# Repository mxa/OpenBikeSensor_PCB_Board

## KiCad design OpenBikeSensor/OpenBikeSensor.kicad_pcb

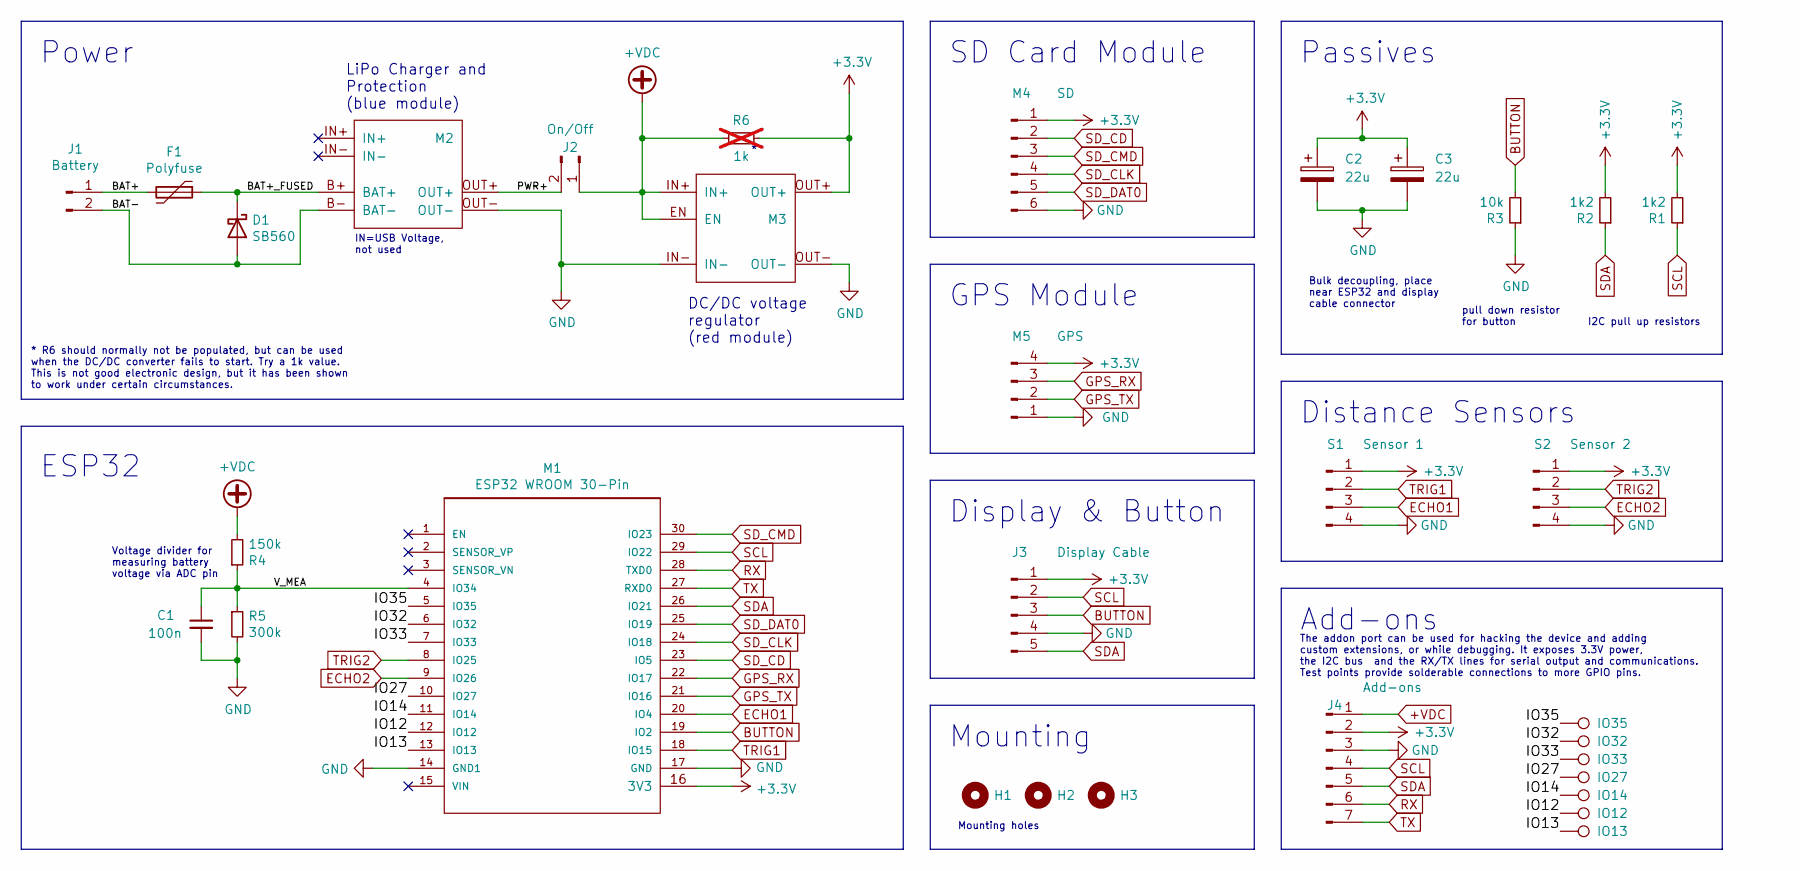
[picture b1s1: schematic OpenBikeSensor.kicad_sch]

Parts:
C1: 100n; C_Disc_D3.0mm_W1.6mm_P2.50mm
C2, C3: 22u; CP_Radial_D4.0mm_P1.50mm
D1: SB560; D_DO-201AD_P5.08mm_Vertical_KathodeUp
F1: Polyfuse; Fuse
H1, H2, H3: MountingHole; MountingHole_3.5mm
IO12: IO12; TestPoint_Pad_D1.0mm
IO13: IO13; TestPoint_Pad_D1.0mm
IO14: IO14; TestPoint_Pad_D1.0mm
IO27: IO27; TestPoint_Pad_D1.0mm
IO32: IO32; TestPoint_Pad_D1.0mm
IO33: IO33; TestPoint_Pad_D1.0mm
IO35: IO35; TestPoint_Pad_D1.0mm
J1: Battery; Connector_1x02
J2: On/Off; Connector_1x02_Switch
J3: Display Cable; Connector_1x05_Display
J4: Add-ons; Connector_1x07
M1: ESP32 WROOM 30-Pin; ESP32_WROOM_30_SMD
M2: LIPoChargerwithProtection; BATTERY-CHARGER-LI-PROT
M3: DCDC_fix; MT3608_SEPIC_DCDC_SMD
M4: SD; Connector_1x06
M5: GPS; Connector_1x04
R1, R2: 1k2; Resistor_Combined_THT3_SMD0805
R3: 10k; Resistor_Combined_THT3_SMD0805
R4: 150k; Resistor_Combined_THT3_SMD0805
R5: 300k; Resistor_Combined_THT3_SMD0805
R6: 1k; R_0603_1608Metric_Pad0.98x0.95mm_HandSolder; not fitted
S1: Sensor 1; Connector_1x04
S2: Sensor 2; Connector_1x04

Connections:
+3.3V: C2.1, C3.1, J3.1, J4.2, M1.16 (3V3), M3.OUT+, M4.1, M5.4, R1.2, R2.2, R6.2, S1.1, S2.1
+VDC: J2.1, J4.1, M3.EN, M3.IN+, R4.2, R6.1
/BAT+: F1.2, J1.1
/BAT+_FUSED: D1.1 (K), F1.1, M2.B+ (BAT+)
/BAT-: D1.2 (A), J1.2, M2.B- (BAT-)
/IO12: IO12.1, M1.12 (IO12)
/IO13: IO13.1, M1.13 (IO13)
/IO14: IO14.1, M1.11 (IO14)
/IO27: IO27.1, M1.10 (IO27)
/IO32: IO32.1, M1.6 (IO32)
/IO33: IO33.1, M1.7 (IO33)
/IO35: IO35.1, M1.5 (IO35)
/PWR+: J2.2, M2.OUT+
/V_MEA: C1.1, M1.4 (IO34), R4.1, R5.1
BUTTON: J3.3, M1.19 (IO2), R3.2
ECHO1: M1.20 (IO4), S1.3
ECHO2: M1.9 (IO26), S2.3
GND: C1.2, C2.2, C3.2, J3.4, J4.3, M1.14 (GND1), M1.17 (GND), M2.OUT-, M3.IN-, M3.OUT-, M4.6, M5.1, R3.1, R5.2, S1.4, S2.4
GPS_RX: M1.22 (IO17), M5.3
GPS_TX: M1.21 (IO16), M5.2
RX: J4.6, M1.28 (TXD0)
SCL: J3.2, J4.4, M1.29 (IO22), R1.1
SDA: J3.5, J4.5, M1.26 (IO21), R2.1
SD_CD: M1.23 (IO5), M4.2
SD_CLK: M1.24 (IO18), M4.4
SD_CMD: M1.30 (IO23), M4.3
SD_DAT0: M1.25 (IO19), M4.5
TRIG1: M1.18 (IO15), S1.2
TRIG2: M1.8 (IO25), S2.2
TX: J4.7, M1.27 (RXD0)

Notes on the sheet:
Mounting holes
Distance Sensors
Voltage divider for measuring battery voltage via ADC pin
Power
DC/DC voltage regulator (red module)
Display & Button
Bulk decoupling, place near ESP32 and display cable connector
Add-ons
GPS Module
pull down resistor for button
Passives
I2C pull up resistors
IN=USB Voltage, not used
Mounting
LiPo Charger and Protection (blue module)
SD Card Module
The addon port can be used for hacking the device and adding custom extensions, or while debugging. It exposes 3.3V power, the I2C bus and the RX/TX lines for serial output and communications. Test points provide solderable connections to more GPIO pins.
ESP32
* R6 should normally not be populated, but can be used when the DC/DC converter fails to start. Try a 1k value. This is not good electronic design, but it has been shown to work under certain circumstances.

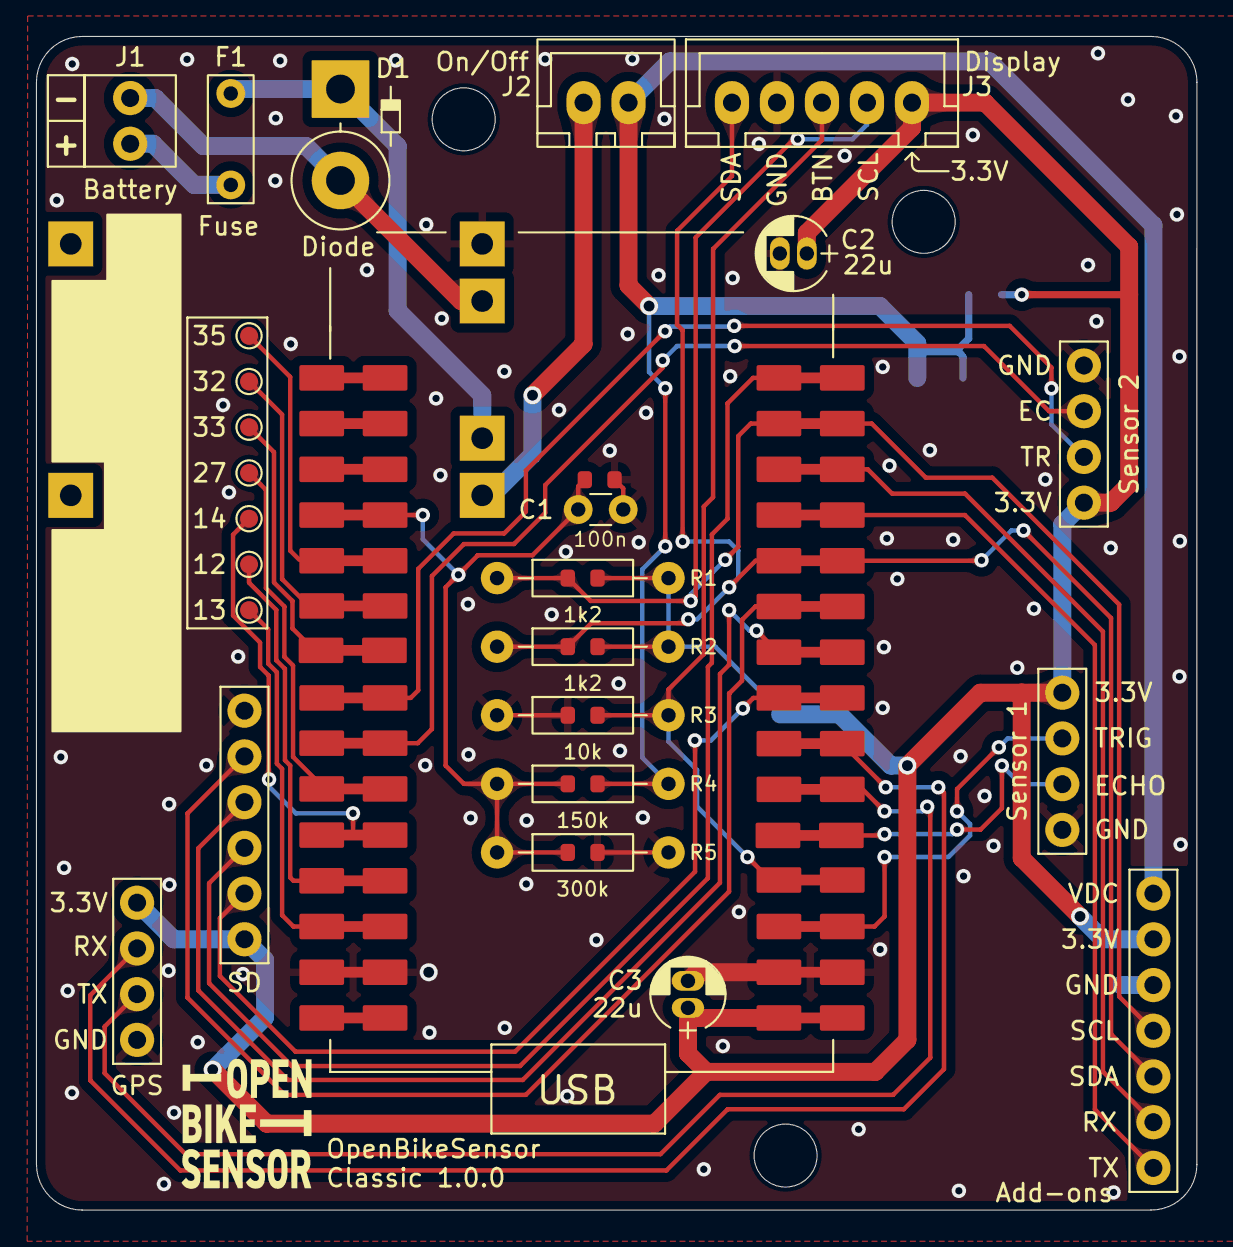
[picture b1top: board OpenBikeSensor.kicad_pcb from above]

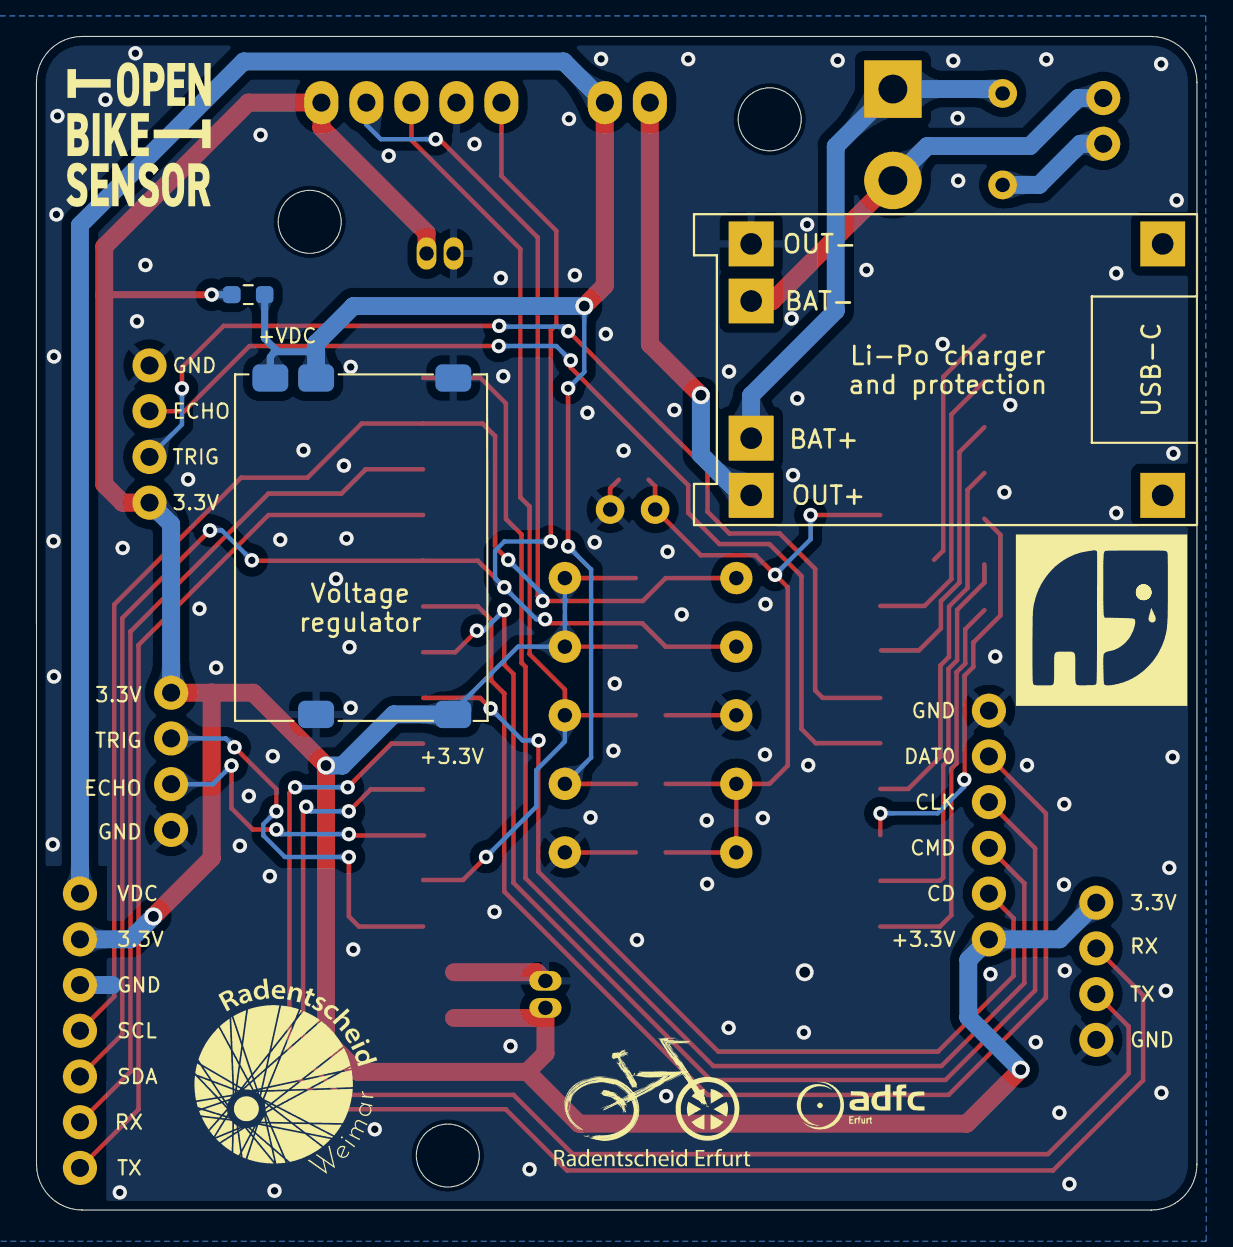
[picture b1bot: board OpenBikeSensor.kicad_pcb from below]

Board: 2 copper layers, 64.5 x 65.2 mm, 32 parts (3 on the bottom side), 30 nets.

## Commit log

2024-01-15 0603 instead of 0805
2024-02-23 natenom träne
